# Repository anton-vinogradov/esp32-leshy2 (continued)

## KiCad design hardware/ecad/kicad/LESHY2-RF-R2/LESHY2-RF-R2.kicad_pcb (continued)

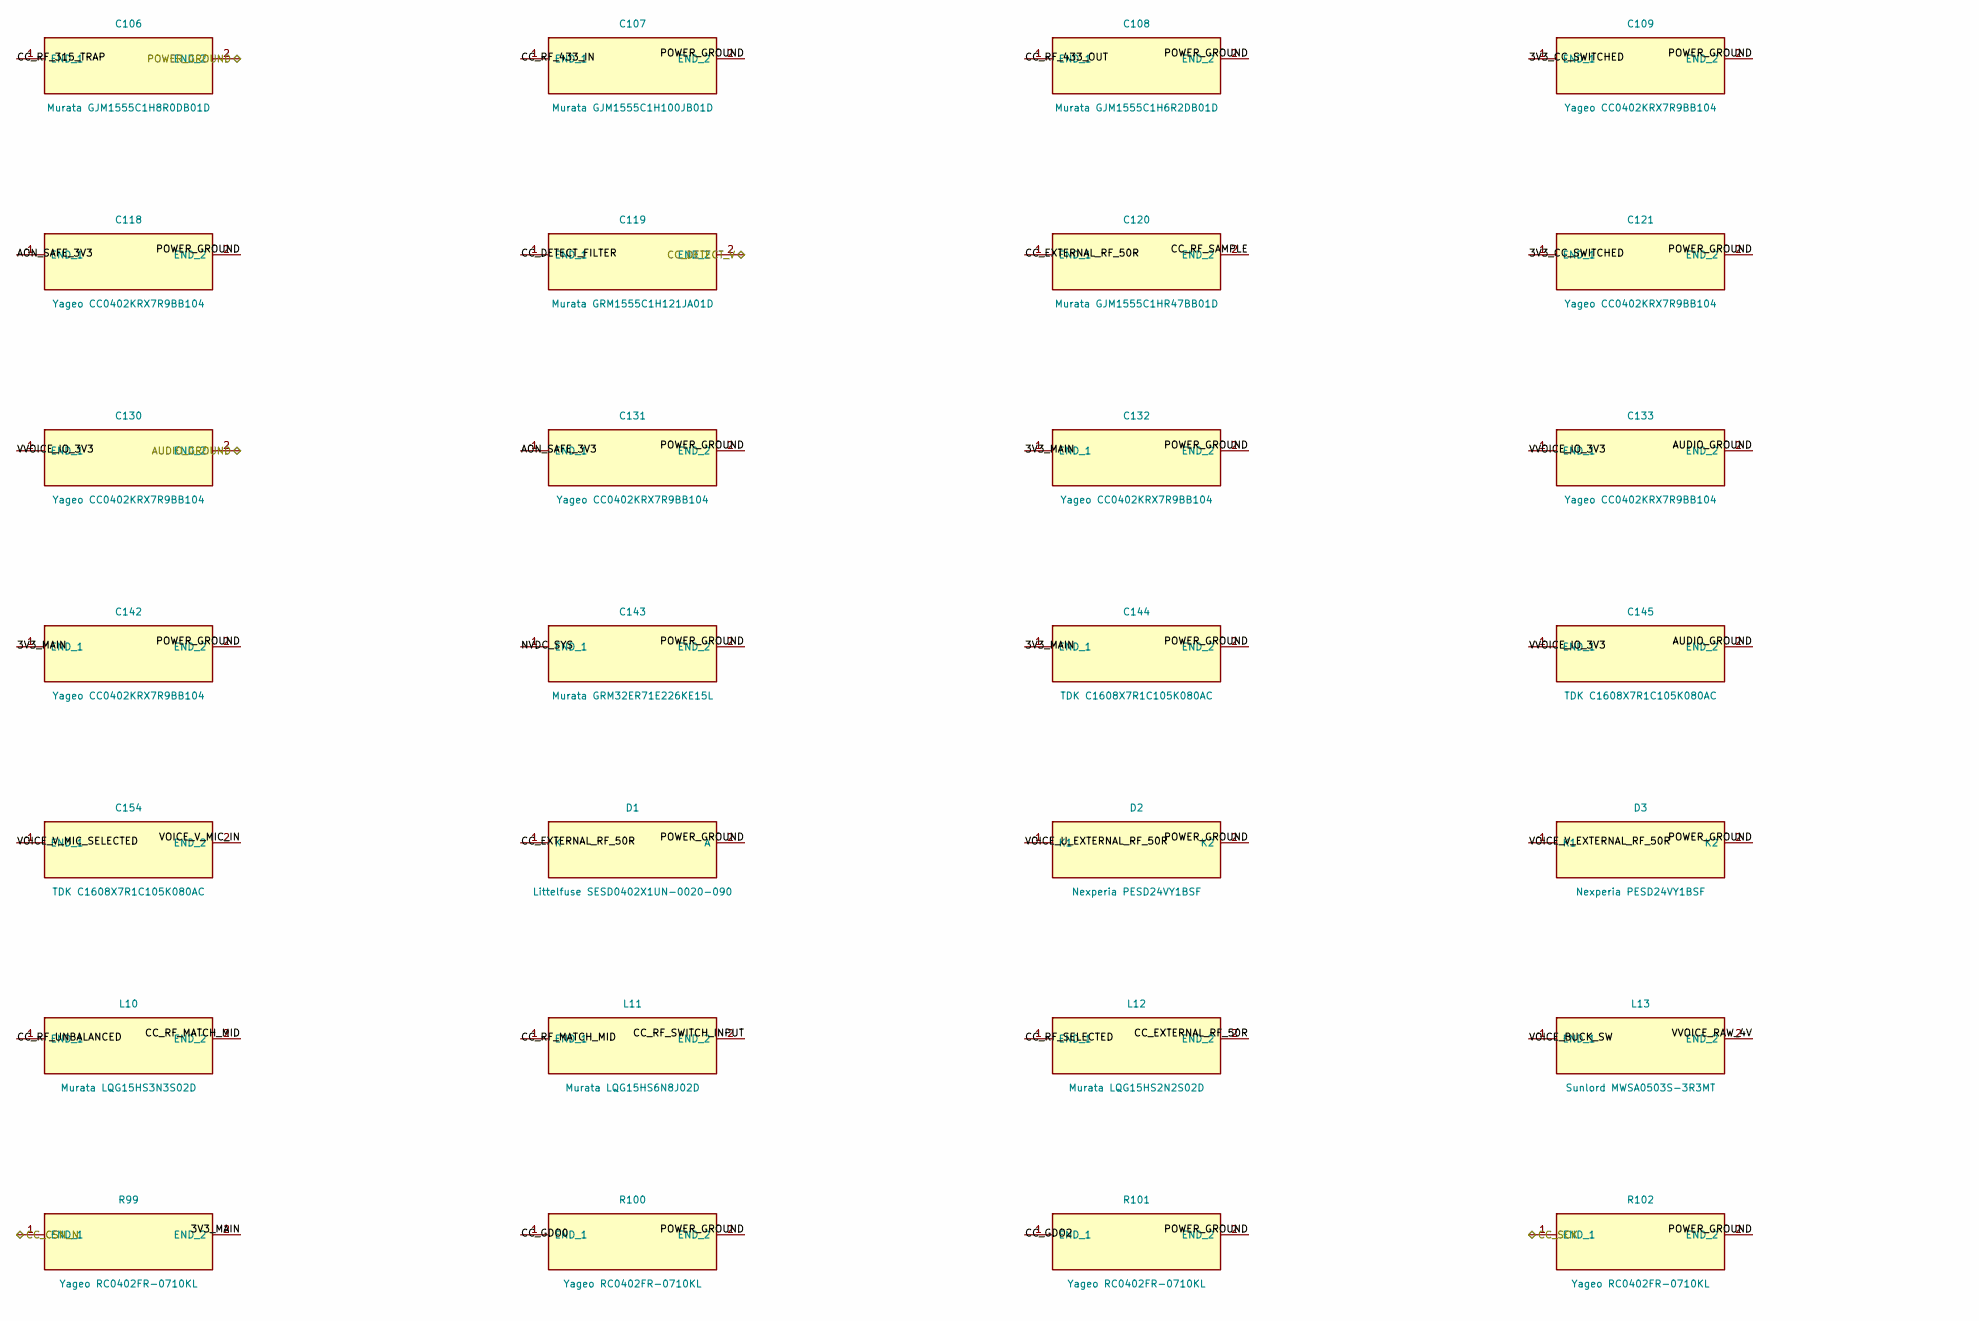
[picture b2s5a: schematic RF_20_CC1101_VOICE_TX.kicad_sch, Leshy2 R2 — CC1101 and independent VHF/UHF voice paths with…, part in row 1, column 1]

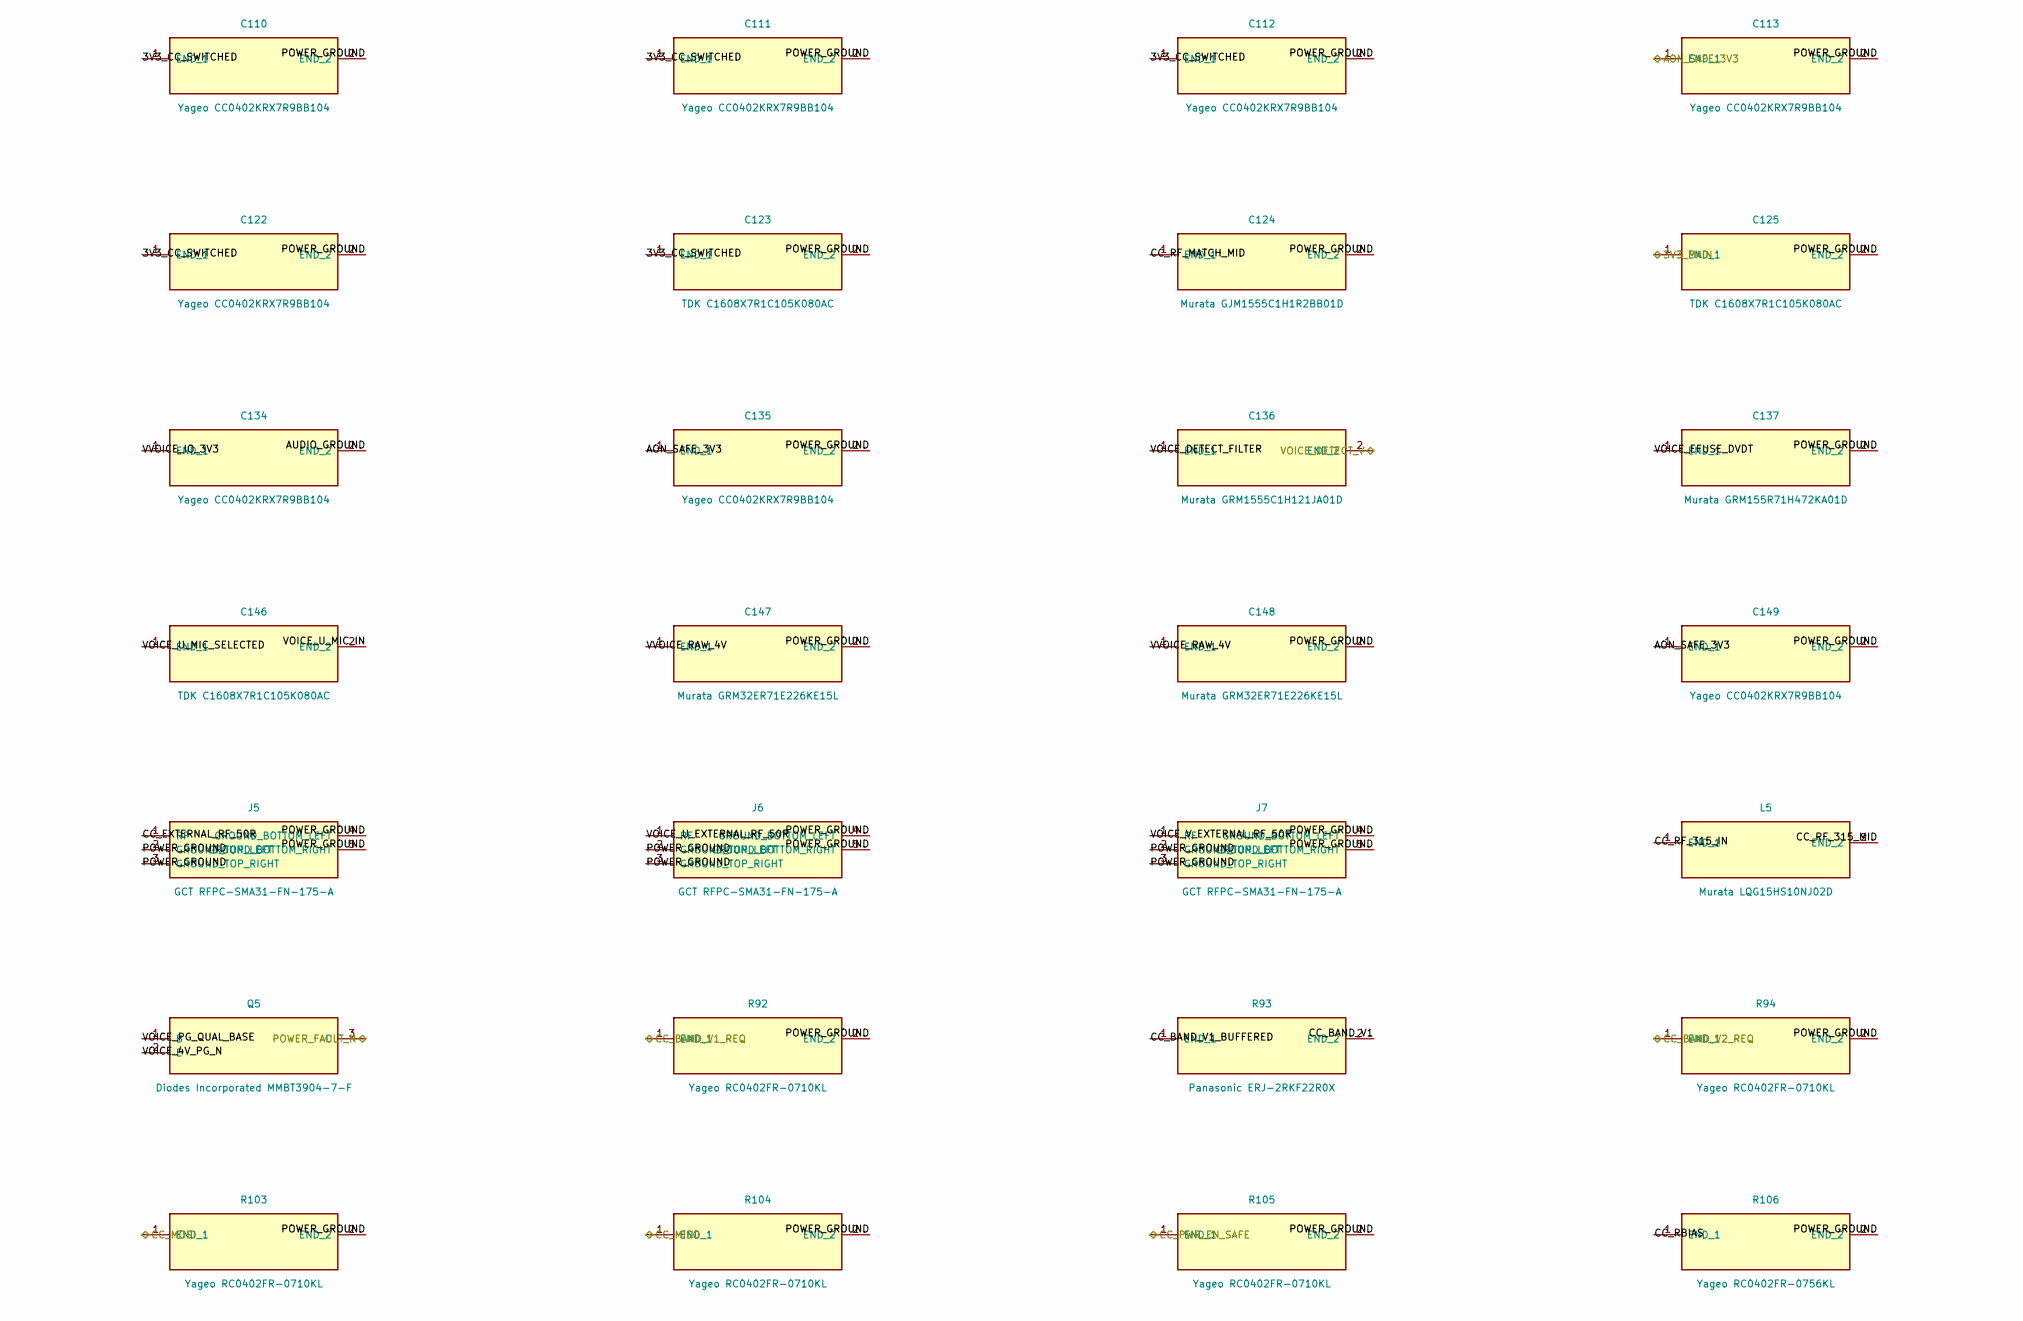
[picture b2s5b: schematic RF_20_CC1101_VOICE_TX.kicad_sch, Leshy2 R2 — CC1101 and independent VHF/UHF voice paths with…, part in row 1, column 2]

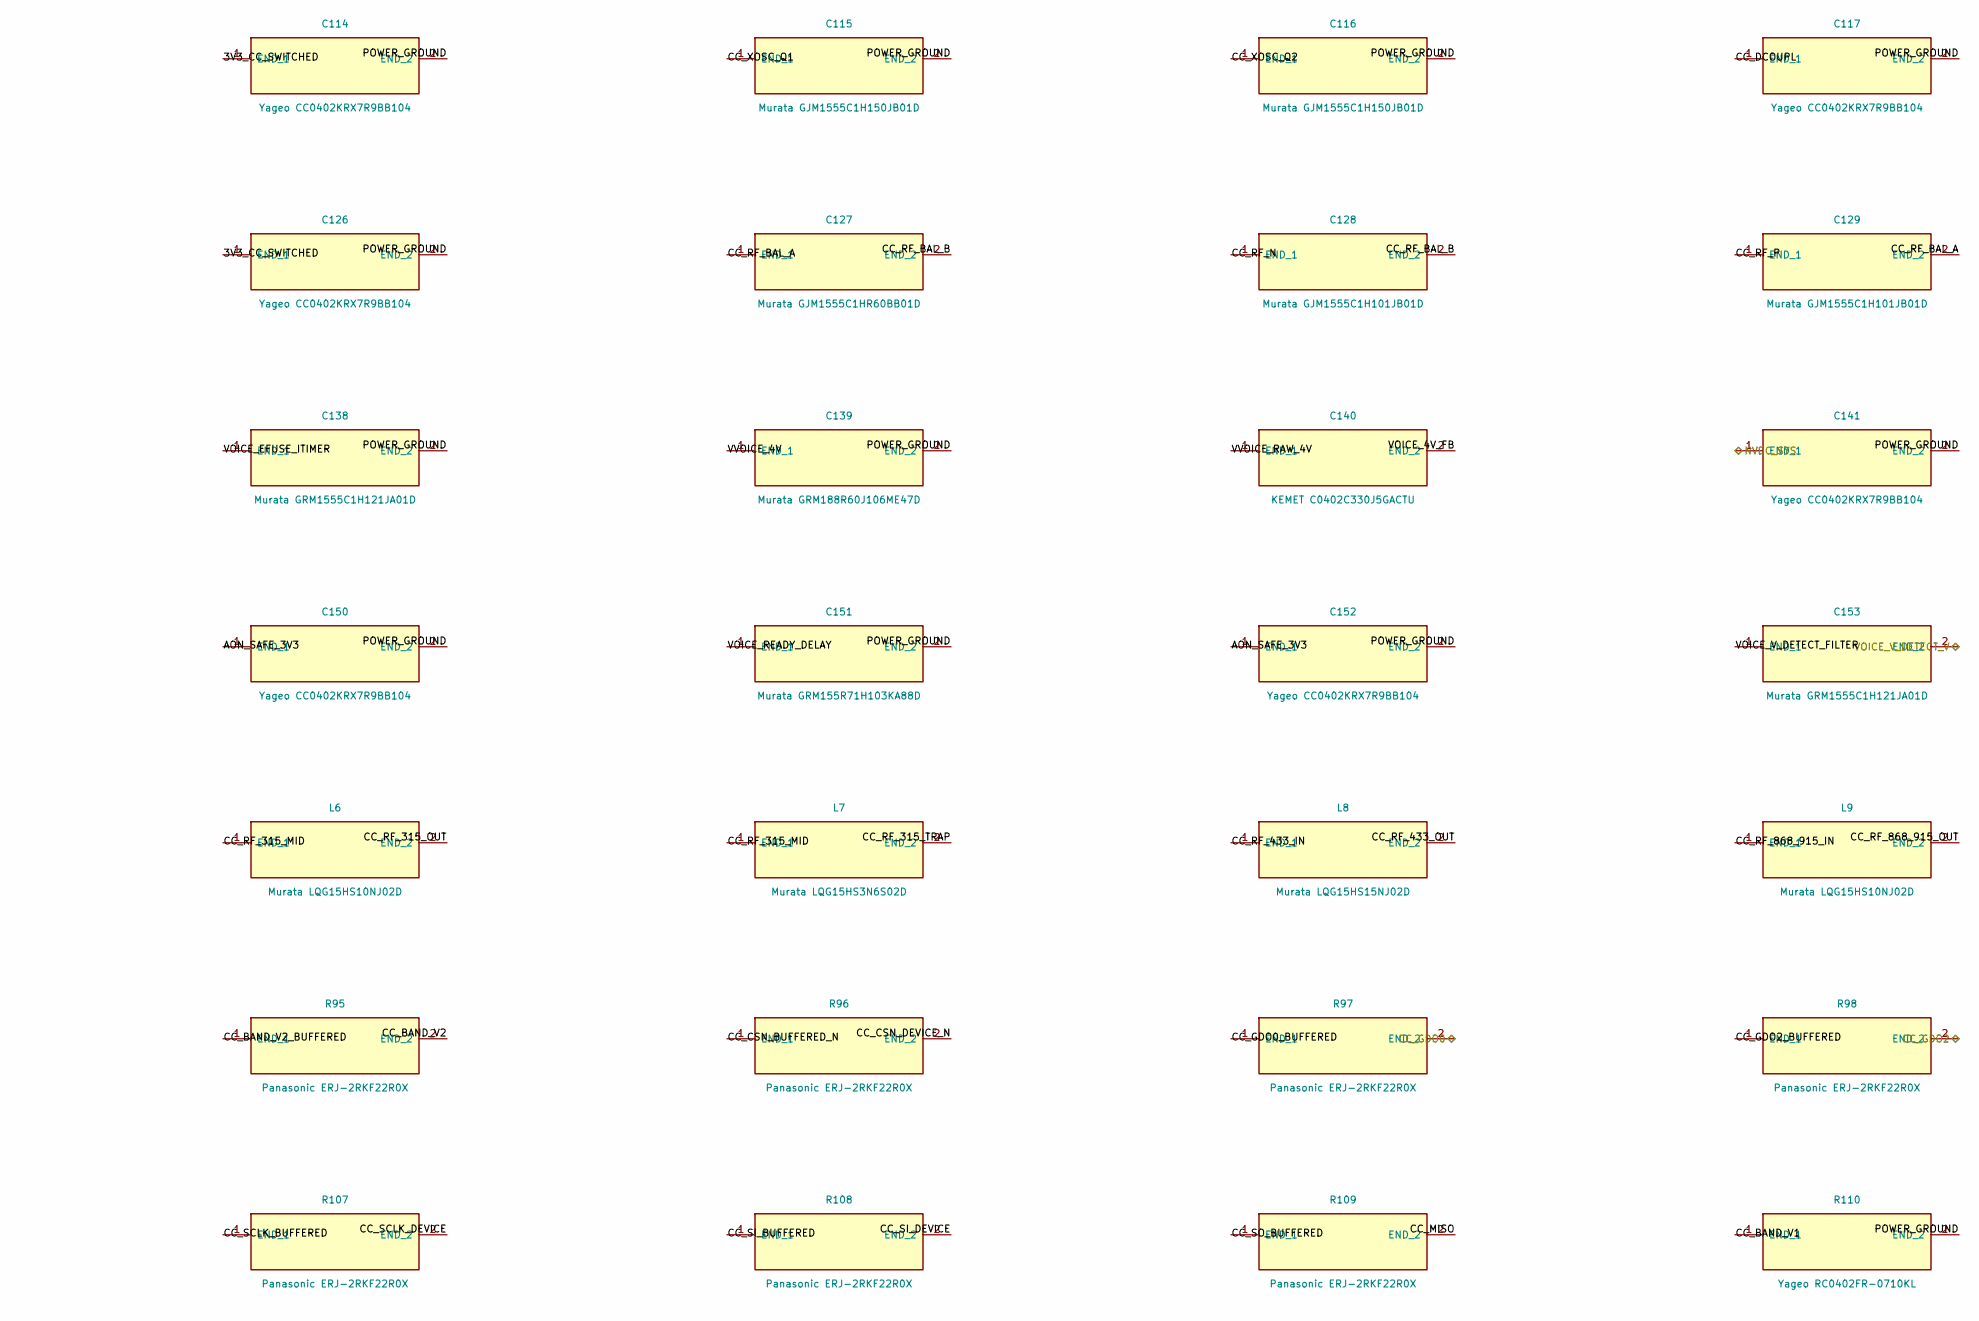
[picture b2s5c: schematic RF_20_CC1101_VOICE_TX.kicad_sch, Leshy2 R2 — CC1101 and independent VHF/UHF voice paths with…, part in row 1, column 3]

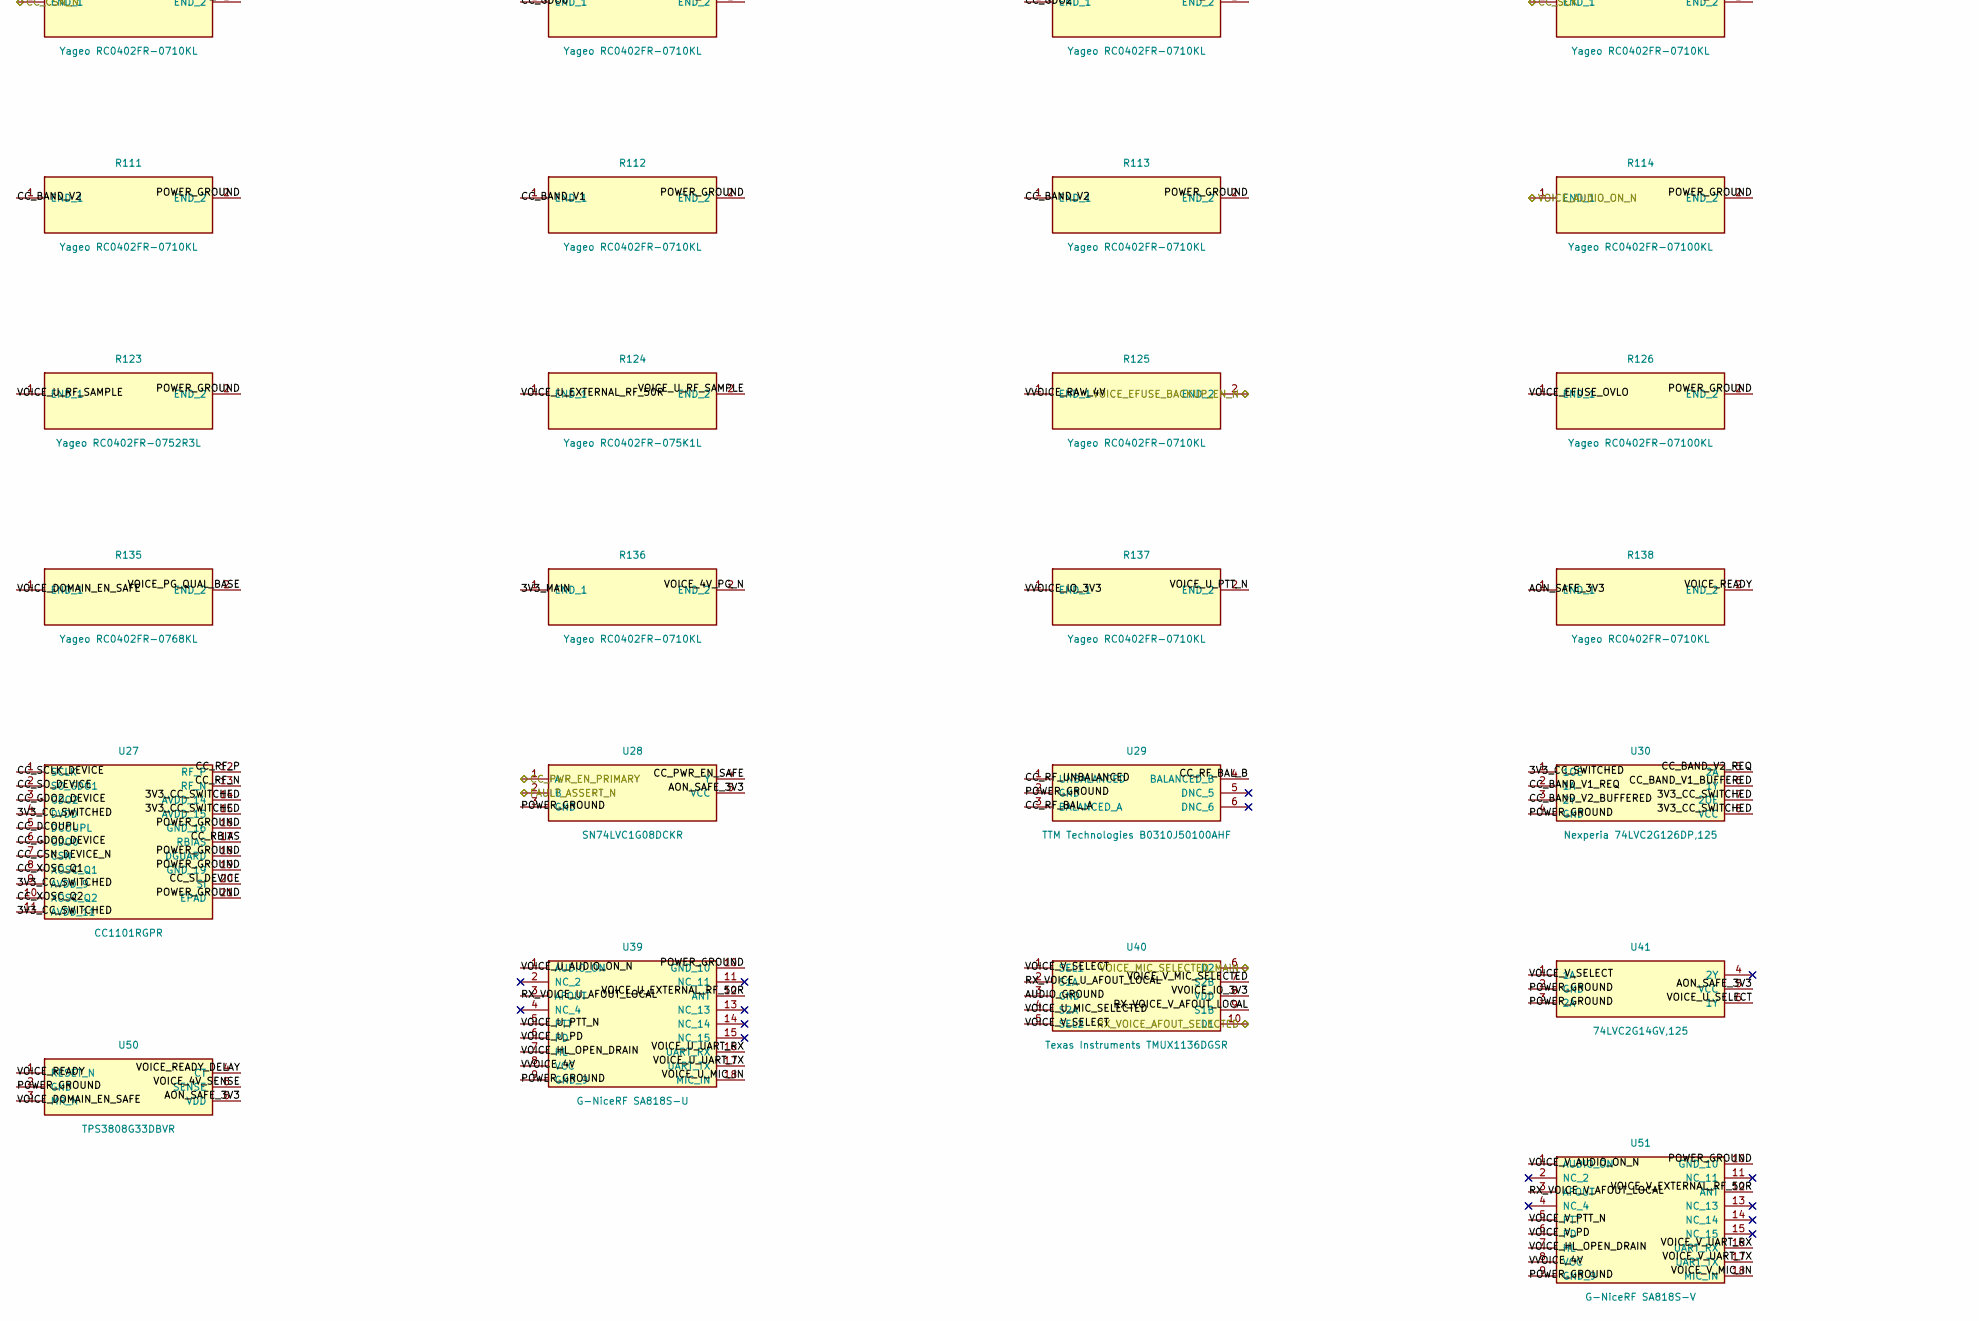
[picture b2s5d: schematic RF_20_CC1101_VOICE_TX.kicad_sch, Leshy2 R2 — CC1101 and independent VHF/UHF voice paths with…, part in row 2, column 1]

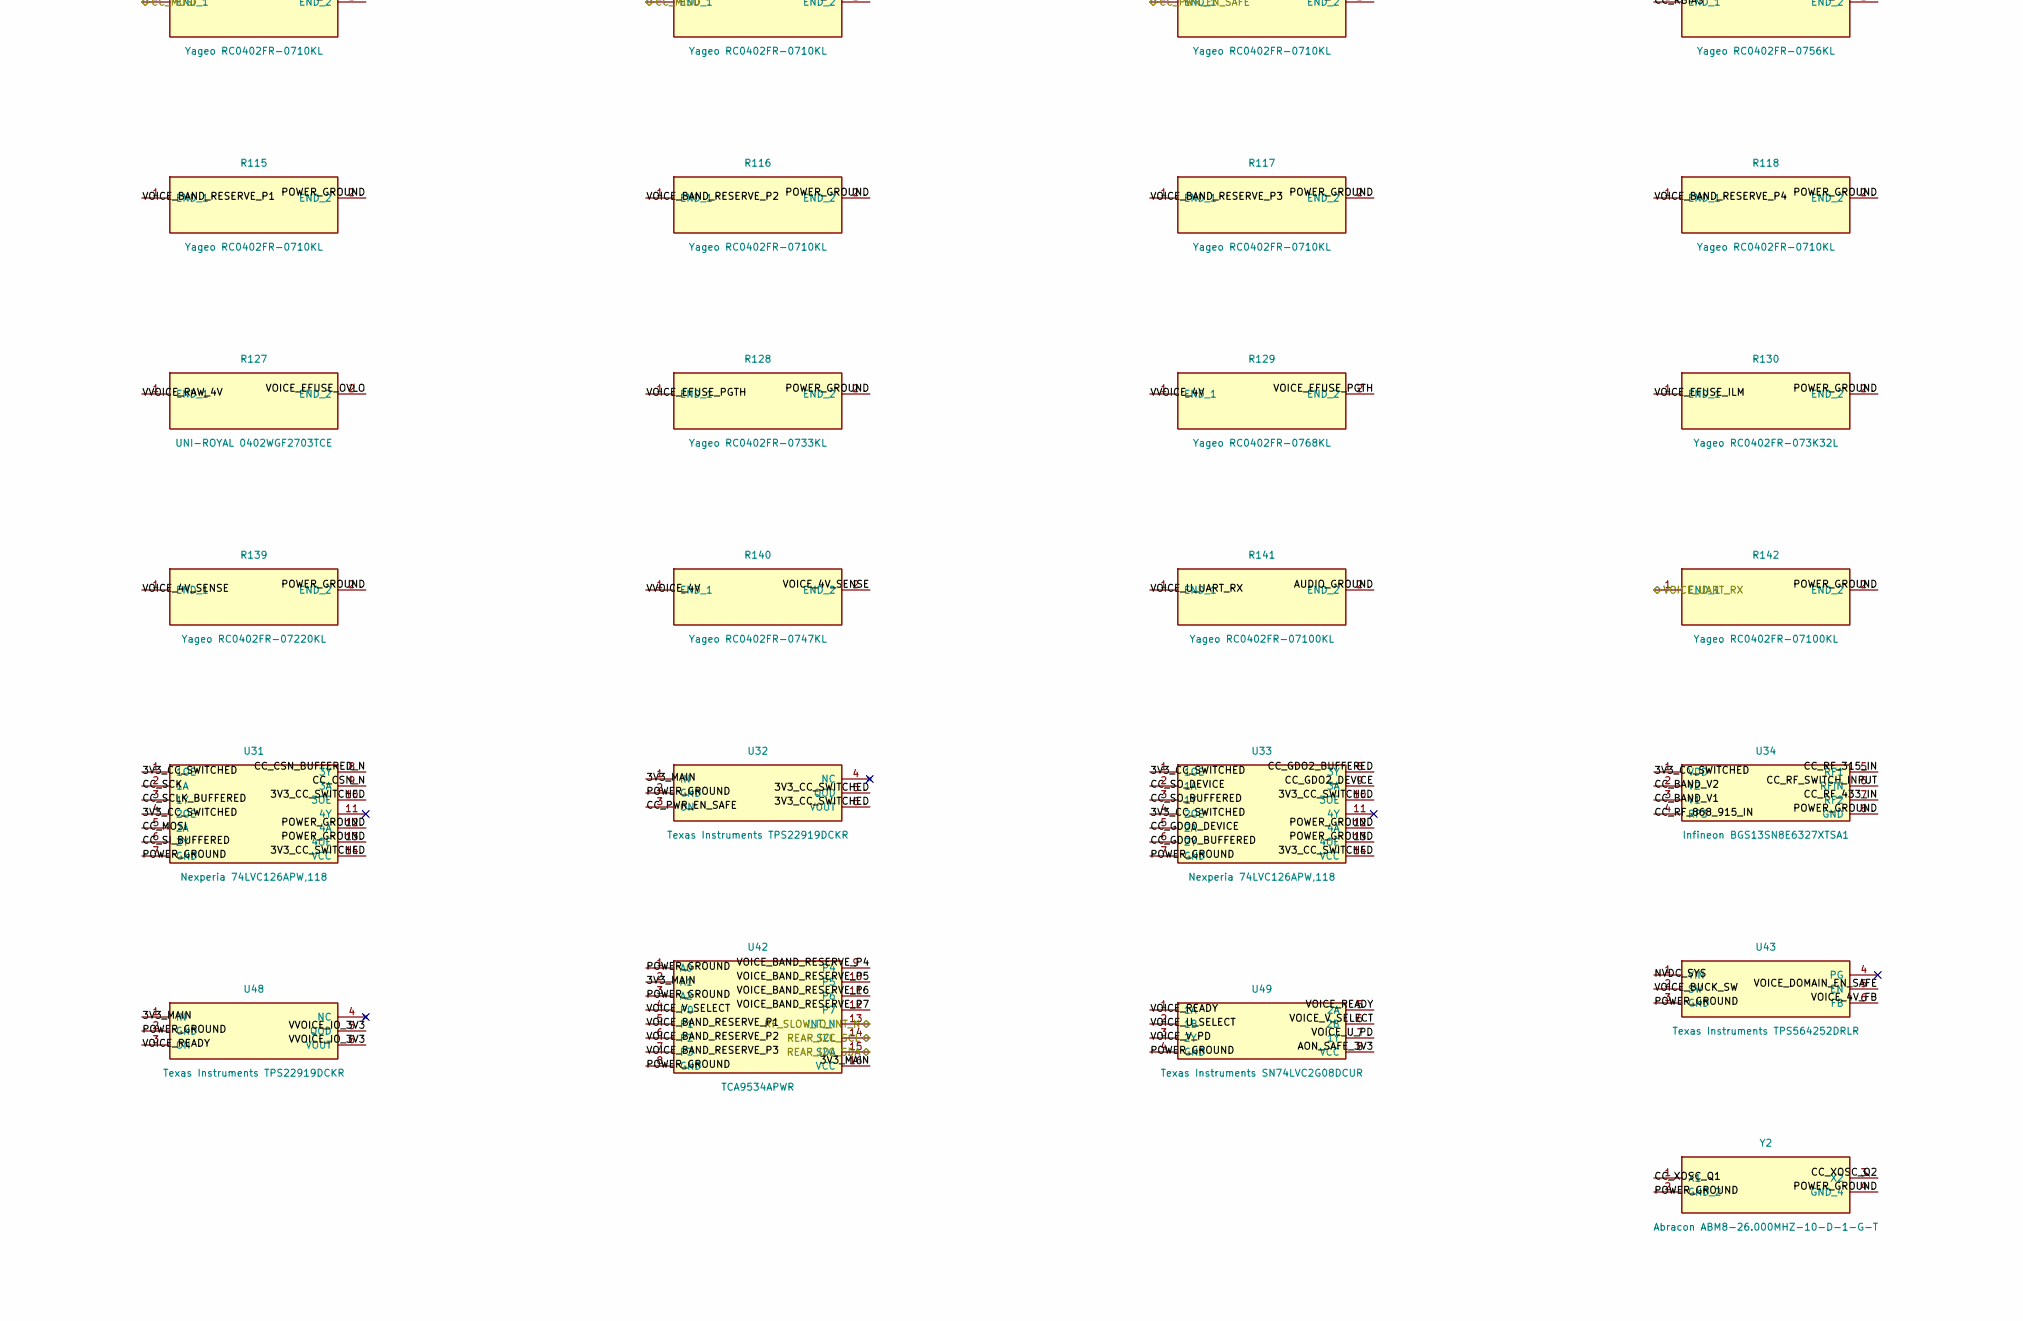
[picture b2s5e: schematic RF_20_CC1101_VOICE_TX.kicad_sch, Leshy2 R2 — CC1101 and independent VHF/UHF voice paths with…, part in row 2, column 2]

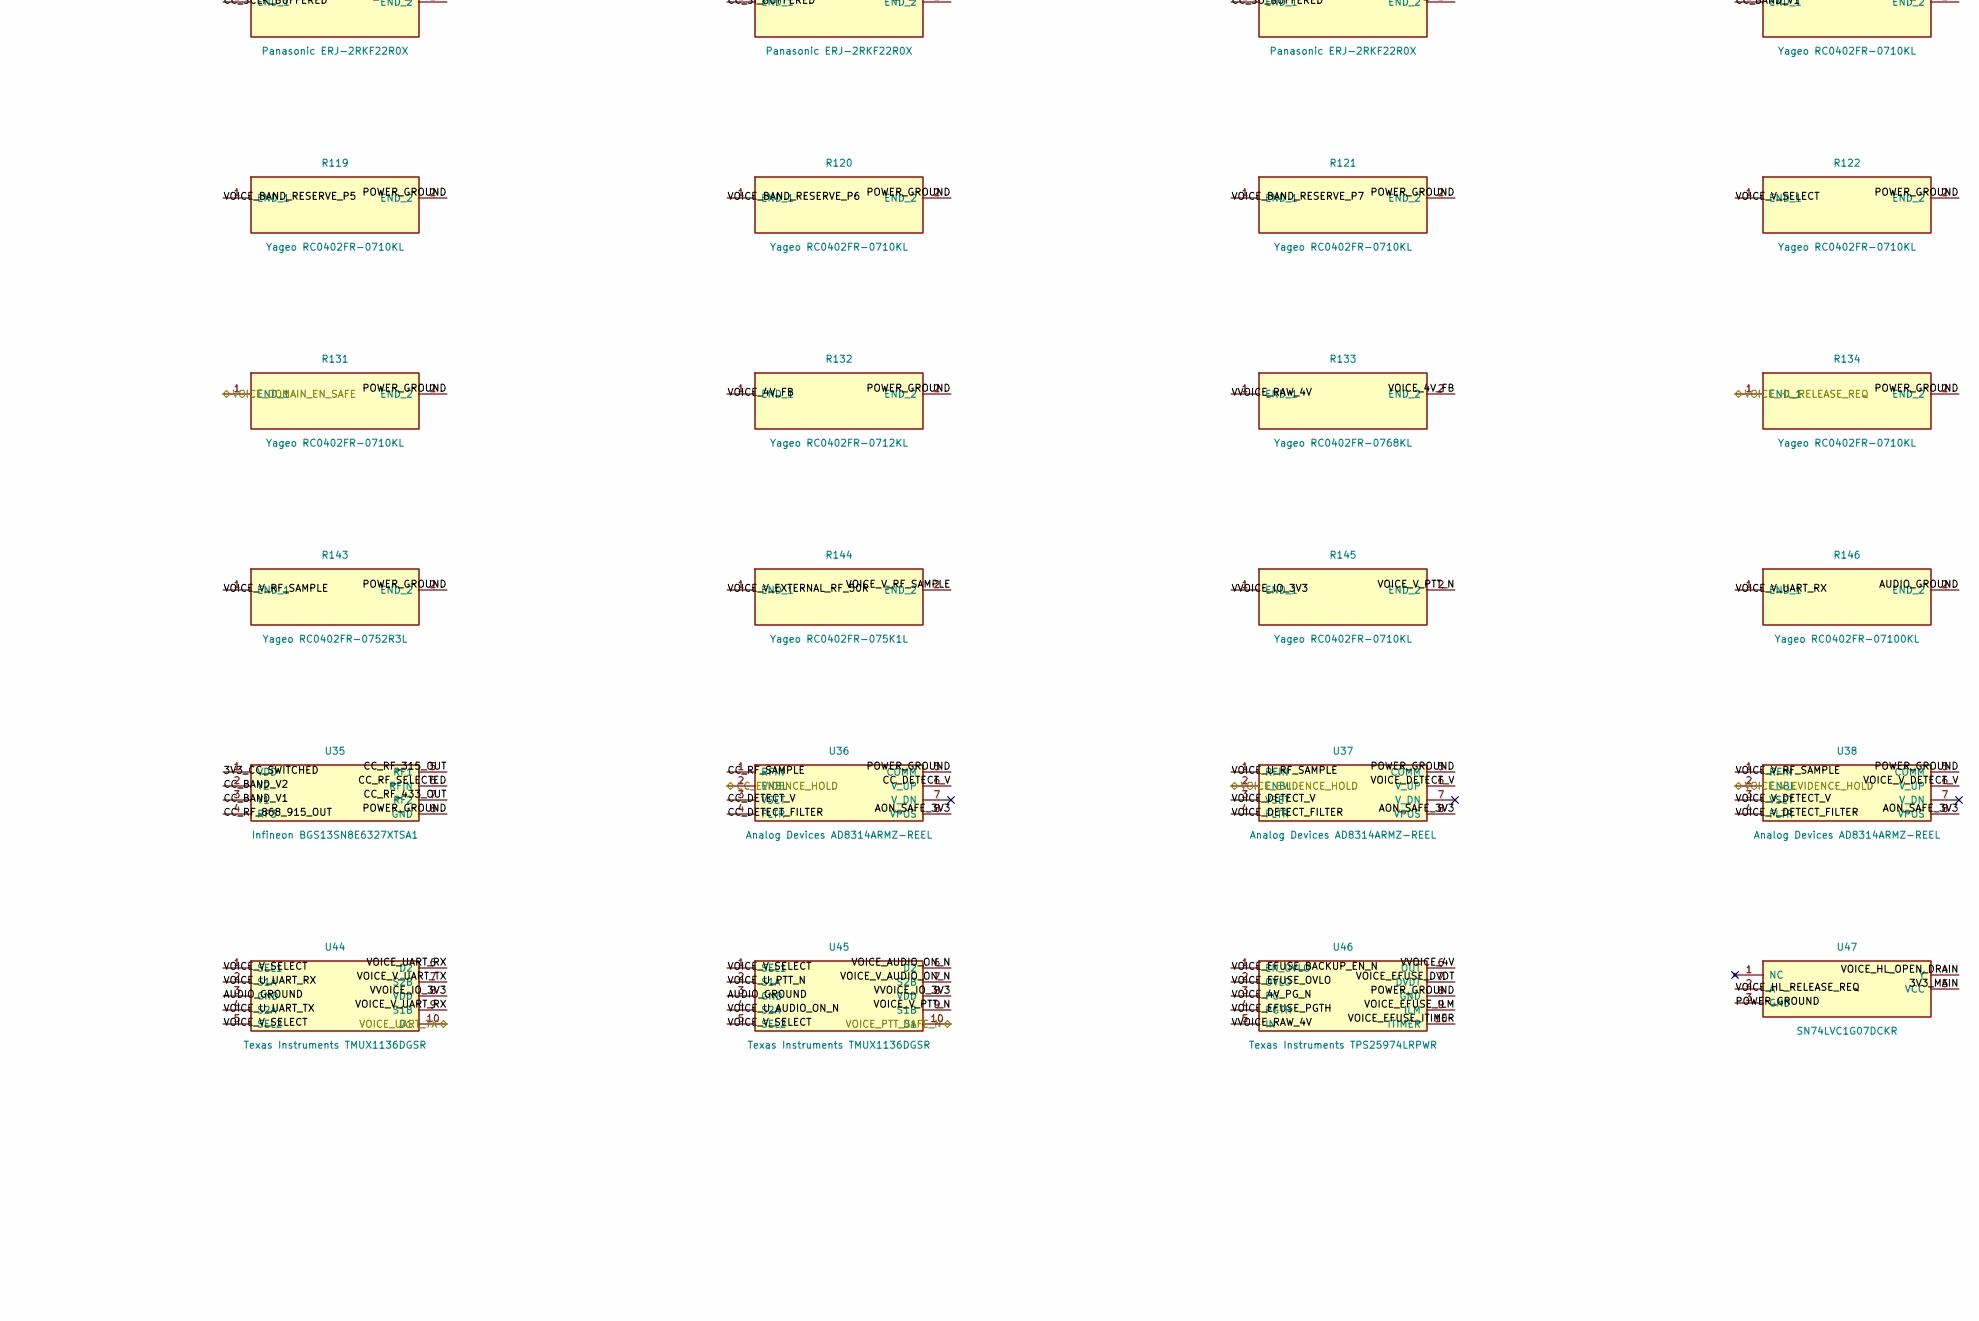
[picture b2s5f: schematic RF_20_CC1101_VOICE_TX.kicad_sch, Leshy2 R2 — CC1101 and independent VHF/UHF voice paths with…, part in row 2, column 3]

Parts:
C106: Murata GJM1555C1H8R0DB01D; C_0402_1005Metric
C107: Murata GJM1555C1H100JB01D; C_0402_1005Metric
C108: Murata GJM1555C1H6R2DB01D; C_0402_1005Metric
C109, C110, C111, C112, C113, C114, C117, C118, C121, C122, C126, C130, C131, C132, C133, C134, C135, C141, C142, C149, C150, C152: Yageo CC0402KRX7R9BB104; C_0402_1005Metric
C115, C116: Murata GJM1555C1H150JB01D; C_0402_1005Metric
C119, C136, C138, C153: Murata GRM1555C1H121JA01D; C_0402_1005Metric
C120: Murata GJM1555C1HR47BB01D; C_0402_1005Metric
C123, C125, C144, C145, C146, C154: TDK C1608X7R1C105K080AC; C_0603_1608Metric
C124: Murata GJM1555C1H1R2BB01D; C_0402_1005Metric
C127: Murata GJM1555C1HR60BB01D; C_0402_1005Metric
C128, C129: Murata GJM1555C1H101JB01D; C_0402_1005Metric
C137: Murata GRM155R71H472KA01D; C_0402_1005Metric
C139: Murata GRM188R60J106ME47D; C_0603_1608Metric
C140: KEMET C0402C330J5GACTU; C_0402_1005Metric
C143, C147, C148: Murata GRM32ER71E226KE15L; C_1210_3225Metric
C151: Murata GRM155R71H103KA88D; C_0402_1005Metric
D1: Littelfuse SESD0402X1UN-0020-090; D_0402_1005Metric
D2, D3: Nexperia PESD24VY1BSF; Nexperia_DSN0603-2_0.6x0.3mm_P0.4mm
J5, J6, J7: GCT RFPC-SMA31-FN-175-A; RFPC-SMA31-FN-175-A
L5, L6, L9: Murata LQG15HS10NJ02D; L_0402_1005Metric
L7: Murata LQG15HS3N6S02D; L_0402_1005Metric
L8: Murata LQG15HS15NJ02D; L_0402_1005Metric
L10: Murata LQG15HS3N3S02D; L_0402_1005Metric
L11: Murata LQG15HS6N8J02D; L_0402_1005Metric
L12: Murata LQG15HS2N2S02D; L_0402_1005Metric
L13: Sunlord MWSA0503S-3R3MT; L_Sunlord_MWSA0503S
Q5: Diodes Incorporated MMBT3904-7-F; SOT-23
R92, R94, R99, R100, R101, R102, R103, R104, R105, R110, R111, R112, R113, R115, R116, R117, R118, R119, R120, R121, R122, R125, R131, R134, R136, R137, R138, R145: Yageo RC0402FR-0710KL; R_0402_1005Metric
R93, R95, R96, R97, R98, R107, R108, R109: Panasonic ERJ-2RKF22R0X; R_0402_1005Metric
R106: Yageo RC0402FR-0756KL; R_0402_1005Metric
R114, R126, R141, R142, R146: Yageo RC0402FR-07100KL; R_0402_1005Metric
R123, R143: Yageo RC0402FR-0752R3L; R_0402_1005Metric
R124, R144: Yageo RC0402FR-075K1L; R_0402_1005Metric
R127: UNI-ROYAL 0402WGF2703TCE; R_0402_1005Metric
R128: Yageo RC0402FR-0733KL; R_0402_1005Metric
R129, R133, R135: Yageo RC0402FR-0768KL; R_0402_1005Metric
R130: Yageo RC0402FR-073K32L; R_0402_1005Metric
R132: Yageo RC0402FR-0712KL; R_0402_1005Metric
R139: Yageo RC0402FR-07220KL; R_0402_1005Metric
R140: Yageo RC0402FR-0747KL; R_0402_1005Metric
U27: CC1101RGPR; Texas_RGP0020D_VQFN-20-1EP_4x4mm_P0.5mm_EP2.7x2.7mm
U28: SN74LVC1G08DCKR; Texas_R-PDSO-G5_DCK-5
U29: TTM Technologies B0310J50100AHF; B0310J50100AHF
U30: Nexperia 74LVC2G126DP,125; TSSOP-8_3x3mm_P0.65mm
U31, U33: Nexperia 74LVC126APW,118; TSSOP-14_4.4x5mm_P0.65mm
U32, U48: Texas Instruments TPS22919DCKR; SOT-363_SC-70-6
U34, U35: Infineon BGS13SN8E6327XTSA1; Infineon-PG-TSNP-8-1
U36, U37, U38: Analog Devices AD8314ARMZ-REEL; MSOP-8_3x3mm_P0.65mm
U39: G-NiceRF SA818S-U; G-NiceRF-SA818S-Official-Package
U40, U44, U45: Texas Instruments TMUX1136DGSR; TSSOP-10_3x3mm_P0.5mm
U41: 74LVC2G14GV,125; SC-74-6_1.55x2.9mm_P0.95mm
U42: TCA9534APWR; TSSOP-16_4.4x5mm_P0.65mm
U43: Texas Instruments TPS564252DRLR; Texas_R-PDSO-N6_DRL-6
U46: Texas Instruments TPS25974LRPWR; TI-RPW0010A-VQFN-HR-10
U47: SN74LVC1G07DCKR; Texas_R-PDSO-G5_DCK-5
U49: Texas Instruments SN74LVC2G08DCUR; VSSOP-8_2.3x2mm_P0.5mm
U50: TPS3808G33DBVR; SOT-23-6
U51: G-NiceRF SA818S-V; G-NiceRF-SA818S-Official-Package
Y2: Abracon ABM8-26.000MHZ-10-D-1-G-T; Crystal_SMD_Abracon_ABM8G-4Pin_3.2x2.5mm

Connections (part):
/RF_01_USB_PD_CHARGE/AON_SAFE_3V3: C113.1 (END_1), C118.1 (END_1), C131.1 (END_1), C135.1 (END_1), C149.1 (END_1), C150.1 (END_1), C152.1 (END_1), R138.1 (END_1), U28.5 (VCC), U36.8 (VPOS), U37.8 (VPOS), U38.8 (VPOS), U41.5 (VCC), U49.8 (VCC), U50.6 (VDD); also elsewhere on the board
/RF_01_USB_PD_CHARGE/NVDC_SYS: C141.1 (END_1), C143.1 (END_1), U43.1 (VIN); also elsewhere on the board
/RF_01_USB_PD_CHARGE/POWER_GROUND: C106.2 (END_2), C107.2 (END_2), C108.2 (END_2), C109.2 (END_2), C110.2 (END_2), C111.2 (END_2), C112.2 (END_2), C113.2 (END_2), C114.2 (END_2), C115.2 (END_2), C116.2 (END_2), C117.2 (END_2), C118.2 (END_2), C121.2 (END_2), C122.2 (END_2), C123.2 (END_2), C124.2 (END_2), C125.2 (END_2), C126.2 (END_2), C131.2 (END_2), C132.2 (END_2), C135.2 (END_2), C137.2 (END_2), C138.2 (END_2), C139.2 (END_2), C141.2 (END_2), C142.2 (END_2), C143.2 (END_2), C144.2 (END_2), C147.2 (END_2), C148.2 (END_2), C149.2 (END_2), C150.2 (END_2), C151.2 (END_2), C152.2 (END_2), D1.2 (A), D2.2 (K2), D3.2 (K2), J5.2 (GROUND_TOP_LEFT), J5.3 (GROUND_TOP_RIGHT), J5.4 (GROUND_BOTTOM_LEFT), J5.5 (GROUND_BOTTOM_RIGHT), J6.2 (GROUND_TOP_LEFT), J6.3 (GROUND_TOP_RIGHT), J6.4 (GROUND_BOTTOM_LEFT), J6.5 (GROUND_BOTTOM_RIGHT), J7.2 (GROUND_TOP_LEFT), J7.3 (GROUND_TOP_RIGHT), J7.4 (GROUND_BOTTOM_LEFT), J7.5 (GROUND_BOTTOM_RIGHT), R92.2 (END_2), R94.2 (END_2), R100.2 (END_2), R101.2 (END_2), R102.2 (END_2), R103.2 (END_2), R104.2 (END_2), R105.2 (END_2), R106.2 (END_2), R110.2 (END_2), R111.2 (END_2), R112.2 (END_2), R113.2 (END_2), R114.2 (END_2), R115.2 (END_2), R116.2 (END_2), R117.2 (END_2), R118.2 (END_2), R119.2 (END_2), R120.2 (END_2), R121.2 (END_2), R122.2 (END_2), R123.2 (END_2), R126.2 (END_2), R128.2 (END_2), R130.2 (END_2), R131.2 (END_2), R132.2 (END_2), R134.2 (END_2), R139.2 (END_2), R142.2 (END_2), R143.2 (END_2), U27.16 (GND_16)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; also elsewhere on the board
/RF_02_PACK_SAFETY_AON/3V3_MAIN: C125.1 (END_1), C132.1 (END_1), C142.1 (END_1), C144.1 (END_1), R99.2 (END_2), R136.1 (END_1), U32.1 (IN), U42.2 (A1), U42.16 (VCC), U47.5 (VCC), U48.1 (IN); also elsewhere on the board
/RF_03_MAIN_RAILS_DOMAIN_GATES/FAULT_ASSERT_N: U28.2 (B); also elsewhere on the board
/RF_03_MAIN_RAILS_DOMAIN_GATES/POWER_FAULT_N: Q5.3 (C); also elsewhere on the board
/RF_10_RP2354_CORE_SERVICE/VOICE_UART_TX: U44.10 (D1); also elsewhere on the board
/RF_20_CC1101_VOICE_TX/3V3_CC_SWITCHED: C109.1 (END_1), C110.1 (END_1), C111.1 (END_1), C112.1 (END_1), C114.1 (END_1), C121.1 (END_1), C122.1 (END_1), C123.1 (END_1), C126.1 (END_1), U27.4 (DVDD), U27.9 (AVDD_9), U27.11 (AVDD_11), U27.14 (AVDD_14), U27.15 (AVDD_15), U30.1 (1OE), U30.7 (2OE), U30.8 (VCC), U31.1 (1OE), U31.4 (2OE), U31.10 (3OE), U31.14 (VCC), U32.5 (QOD), U32.6 (VOUT), U33.1 (1OE), U33.4 (2OE), U33.10 (3OE), U33.14 (VCC), U34.1 (VDD), U35.1 (VDD)
/RF_20_CC1101_VOICE_TX/AUDIO_GROUND: C130.2 (END_2), C133.2 (END_2), C134.2 (END_2), C145.2 (END_2), R141.2 (END_2), R146.2 (END_2), U40.3 (GND), U44.3 (GND), U45.3 (GND); also elsewhere on the board
/RF_20_CC1101_VOICE_TX/CC_BAND_V1: R93.2 (END_2), R110.1 (END_1), R112.1 (END_1), U34.3 (V1), U35.3 (V1)
/RF_20_CC1101_VOICE_TX/CC_BAND_V1_BUFFERED: R93.1 (END_1), U30.6 (1Y)
/RF_20_CC1101_VOICE_TX/CC_BAND_V1_REQ: R92.1 (END_1), U30.2 (1A); also elsewhere on the board
/RF_20_CC1101_VOICE_TX/CC_BAND_V2: R95.2 (END_2), R111.1 (END_1), R113.1 (END_1), U34.2 (V2), U35.2 (V2)
/RF_20_CC1101_VOICE_TX/CC_BAND_V2_BUFFERED: R95.1 (END_1), U30.3 (2Y)
/RF_20_CC1101_VOICE_TX/CC_BAND_V2_REQ: R94.1 (END_1), U30.5 (2A); also elsewhere on the board
/RF_20_CC1101_VOICE_TX/CC_CSN_BUFFERED_N: R96.1 (END_1), U31.8 (3Y)
/RF_20_CC1101_VOICE_TX/CC_CSN_DEVICE_N: R96.2 (END_2), U27.7 (CSN)
/RF_20_CC1101_VOICE_TX/CC_CSN_N: R99.1 (END_1), U31.9 (3A); also elsewhere on the board
/RF_20_CC1101_VOICE_TX/CC_DCOUPL: C117.1 (END_1), U27.5 (DCOUPL)
/RF_20_CC1101_VOICE_TX/CC_DETECT_FILTER: C119.1 (END_1), U36.4 (FLTR)
/RF_20_CC1101_VOICE_TX/CC_DETECT_V: C119.2 (END_2), U36.3 (VSET), U36.6 (V_UP); also elsewhere on the board
/RF_20_CC1101_VOICE_TX/CC_EXTERNAL_RF_50R: C120.1 (END_1), D1.1 (K), J5.1 (RF), L12.2 (END_2)
/RF_20_CC1101_VOICE_TX/CC_GDO0: R97.2 (END_2), R100.1 (END_1); also elsewhere on the board
/RF_20_CC1101_VOICE_TX/CC_GDO0_BUFFERED: R97.1 (END_1), U33.6 (2Y)
/RF_20_CC1101_VOICE_TX/CC_GDO0_DEVICE: U27.6 (GDO0), U33.5 (2A)
/RF_20_CC1101_VOICE_TX/CC_GDO2: R98.2 (END_2), R101.1 (END_1); also elsewhere on the board
/RF_20_CC1101_VOICE_TX/CC_GDO2_BUFFERED: R98.1 (END_1), U33.8 (3Y)
/RF_20_CC1101_VOICE_TX/CC_GDO2_DEVICE: U27.3 (GDO2), U33.9 (3A)
/RF_20_CC1101_VOICE_TX/CC_MISO: R104.1 (END_1), R109.2 (END_2); also elsewhere on the board
/RF_20_CC1101_VOICE_TX/CC_MOSI: R103.1 (END_1), U31.5 (2A); also elsewhere on the board
/RF_20_CC1101_VOICE_TX/CC_PWR_EN_PRIMARY: U28.1 (A); also elsewhere on the board
/RF_20_CC1101_VOICE_TX/CC_PWR_EN_SAFE: R105.1 (END_1), U28.4 (Y), U32.3 (ON); also elsewhere on the board
/RF_20_CC1101_VOICE_TX/CC_RBIAS: R106.1 (END_1), U27.17 (RBIAS)
/RF_20_CC1101_VOICE_TX/CC_RF_315_IN: L5.1 (END_1), U34.5 (RF1)
/RF_20_CC1101_VOICE_TX/CC_RF_315_MID: L5.2 (END_2), L6.1 (END_1), L7.1 (END_1)
/RF_20_CC1101_VOICE_TX/CC_RF_315_OUT: L6.2 (END_2), U35.5 (RF1)
/RF_20_CC1101_VOICE_TX/CC_RF_315_TRAP: C106.1 (END_1), L7.2 (END_2)
/RF_20_CC1101_VOICE_TX/CC_RF_433_IN: C107.1 (END_1), L8.1 (END_1), U34.7 (RF2)
/RF_20_CC1101_VOICE_TX/CC_RF_433_OUT: C108.1 (END_1), L8.2 (END_2), U35.7 (RF2)
/RF_20_CC1101_VOICE_TX/CC_RF_868_915_IN: L9.1 (END_1), U34.4 (RF3)
/RF_20_CC1101_VOICE_TX/CC_RF_868_915_OUT: L9.2 (END_2), U35.4 (RF3)
/RF_20_CC1101_VOICE_TX/CC_RF_BAL_A: C127.1 (END_1), C129.2 (END_2), U29.3 (BALANCED_A)
/RF_20_CC1101_VOICE_TX/CC_RF_BAL_B: C127.2 (END_2), C128.2 (END_2), U29.4 (BALANCED_B)
/RF_20_CC1101_VOICE_TX/CC_RF_MATCH_MID: C124.1 (END_1), L10.2 (END_2), L11.1 (END_1)
/RF_20_CC1101_VOICE_TX/CC_RF_N: C128.1 (END_1), U27.13 (RF_N)
/RF_20_CC1101_VOICE_TX/CC_RF_P: C129.1 (END_1), U27.12 (RF_P)
/RF_20_CC1101_VOICE_TX/CC_RF_SAMPLE: C120.2 (END_2), U36.1 (RFIN)
/RF_20_CC1101_VOICE_TX/CC_RF_SELECTED: L12.1 (END_1), U35.6 (RFIN)
/RF_20_CC1101_VOICE_TX/CC_RF_SWITCH_INPUT: L11.2 (END_2), U34.6 (RFIN)
/RF_20_CC1101_VOICE_TX/CC_RF_UNBALANCED: L10.1 (END_1), U29.1 (UNBALANCED)
/RF_20_CC1101_VOICE_TX/CC_SCK: R102.1 (END_1), U31.2 (1A); also elsewhere on the board
/RF_20_CC1101_VOICE_TX/CC_SCLK_BUFFERED: R107.1 (END_1), U31.3 (1Y)
/RF_20_CC1101_VOICE_TX/CC_SCLK_DEVICE: R107.2 (END_2), U27.1 (SCLK)
/RF_20_CC1101_VOICE_TX/CC_SI_BUFFERED: R108.1 (END_1), U31.6 (2Y)
/RF_20_CC1101_VOICE_TX/CC_SI_DEVICE: R108.2 (END_2), U27.20 (SI)
/RF_20_CC1101_VOICE_TX/CC_SO_BUFFERED: R109.1 (END_1), U33.3 (1Y)
/RF_20_CC1101_VOICE_TX/CC_SO_DEVICE: U27.2 (SO_GDO1), U33.2 (1A)
/RF_20_CC1101_VOICE_TX/CC_XOSC_Q1: C115.1 (END_1), U27.8 (XOSC_Q1), Y2.1 (X1)
/RF_20_CC1101_VOICE_TX/CC_XOSC_Q2: C116.1 (END_1), U27.10 (XOSC_Q2), Y2.3 (X2)
/RF_20_CC1101_VOICE_TX/RX_VOICE_AFOUT_SELECTED: U40.10 (D1); also elsewhere on the board
/RF_20_CC1101_VOICE_TX/RX_VOICE_U_AFOUT_LOCAL: U39.3 (AFOUT), U40.2 (S1A)
/RF_20_CC1101_VOICE_TX/RX_VOICE_V_AFOUT_LOCAL: U40.9 (S1B), U51.3 (AFOUT)
/RF_20_CC1101_VOICE_TX/VOICE_4V_FB: C140.2 (END_2), R132.1 (END_1), R133.2 (END_2), U43.6 (FB)
/RF_20_CC1101_VOICE_TX/VOICE_4V_PG_N: Q5.2 (E), R136.2 (END_2), U46.3 (PG)
/RF_20_CC1101_VOICE_TX/VOICE_4V_SENSE: R139.1 (END_1), R140.2 (END_2), U50.5 (SENSE)
/RF_20_CC1101_VOICE_TX/VOICE_AUDIO_ON_N: R114.1 (END_1), U45.6 (D2); also elsewhere on the board
/RF_20_CC1101_VOICE_TX/VOICE_BAND_RESERVE_P1: R115.1 (END_1), U42.5 (P1)
/RF_20_CC1101_VOICE_TX/VOICE_BAND_RESERVE_P2: R116.1 (END_1), U42.6 (P2)
/RF_20_CC1101_VOICE_TX/VOICE_BAND_RESERVE_P3: R117.1 (END_1), U42.7 (P3)
/RF_20_CC1101_VOICE_TX/VOICE_BAND_RESERVE_P4: R118.1 (END_1), U42.9 (P4)
/RF_20_CC1101_VOICE_TX/VOICE_BAND_RESERVE_P5: R119.1 (END_1), U42.10 (P5)
/RF_20_CC1101_VOICE_TX/VOICE_BAND_RESERVE_P6: R120.1 (END_1), U42.11 (P6)
/RF_20_CC1101_VOICE_TX/VOICE_BAND_RESERVE_P7: R121.1 (END_1), U42.12 (P7)
/RF_20_CC1101_VOICE_TX/VOICE_BUCK_SW: L13.1 (END_1), U43.2 (SW)
/RF_20_CC1101_VOICE_TX/VOICE_DETECT_FILTER: C136.1 (END_1), U37.4 (FLTR)
/RF_20_CC1101_VOICE_TX/VOICE_DETECT_V: C136.2 (END_2), U37.3 (VSET), U37.6 (V_UP); also elsewhere on the board
/RF_20_CC1101_VOICE_TX/VOICE_DOMAIN_EN_SAFE: R131.1 (END_1), R135.1 (END_1), U43.5 (EN), U50.3 (MR_N); also elsewhere on the board
/RF_20_CC1101_VOICE_TX/VOICE_EFUSE_BACKUP_EN_N: R125.2 (END_2), U46.1 (EN_UVLO); also elsewhere on the board
/RF_20_CC1101_VOICE_TX/VOICE_EFUSE_DVDT: C137.1 (END_1), U46.7 (DVDT)
/RF_20_CC1101_VOICE_TX/VOICE_EFUSE_ILM: R130.1 (END_1), U46.9 (ILM)
/RF_20_CC1101_VOICE_TX/VOICE_EFUSE_ITIMER: C138.1 (END_1), U46.10 (ITIMER)
/RF_20_CC1101_VOICE_TX/VOICE_EFUSE_OVLO: R126.1 (END_1), R127.2 (END_2), U46.2 (OVLO)
/RF_20_CC1101_VOICE_TX/VOICE_EFUSE_PGTH: R128.1 (END_1), R129.2 (END_2), U46.4 (PGTH)
/RF_20_CC1101_VOICE_TX/VOICE_HL_OPEN_DRAIN: U39.7 (HL), U47.4 (Y), U51.7 (HL)
/RF_20_CC1101_VOICE_TX/VOICE_HL_RELEASE_REQ: R134.1 (END_1), U47.2 (A); also elsewhere on the board
/RF_20_CC1101_VOICE_TX/VOICE_MIC_SELECTED_MAIN: U40.6 (D2); also elsewhere on the board
/RF_20_CC1101_VOICE_TX/VOICE_PG_QUAL_BASE: Q5.1 (B), R135.2 (END_2)
/RF_20_CC1101_VOICE_TX/VOICE_PTT_SAFE_N: U45.10 (D1); also elsewhere on the board
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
